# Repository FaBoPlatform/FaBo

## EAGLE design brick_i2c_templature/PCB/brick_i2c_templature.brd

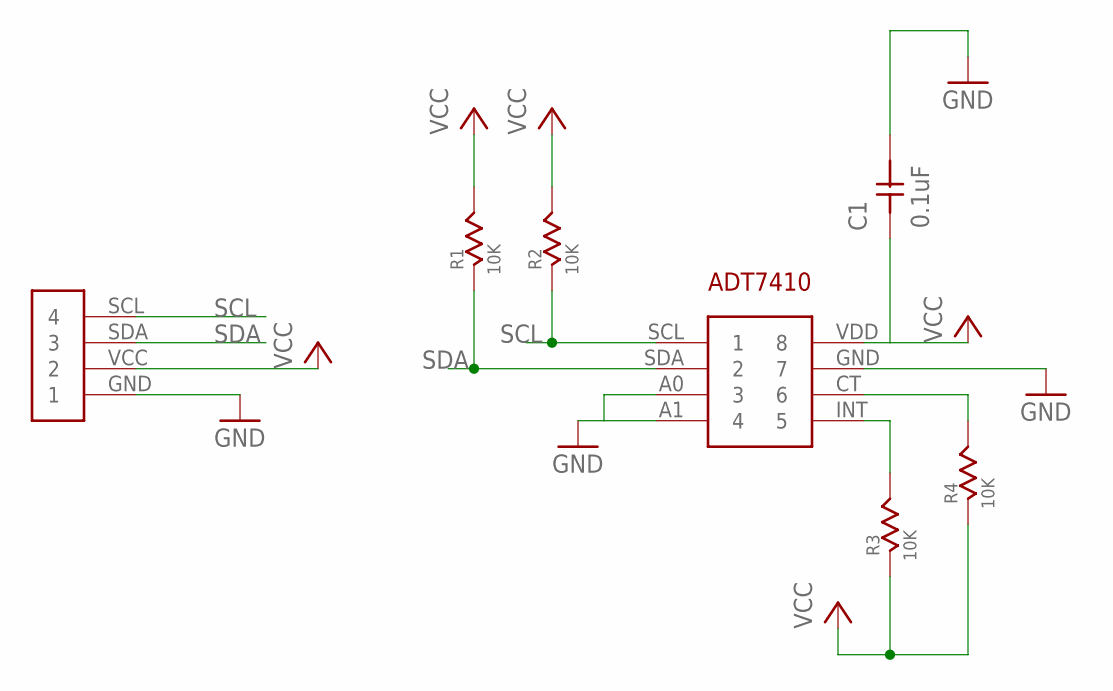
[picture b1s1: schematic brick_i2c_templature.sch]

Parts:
C1: 0.1uF; RESISTOR_0603
R1, R2, R3, R4: 10K; RESISTOR_0603
U$1: I2C-ADT7410
U$2: BRICK_I2C

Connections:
GND: C1.P$2, U$1.A0 (3), U$1.A1 (4), U$1.GND (7), U$2.GND (1)
unnamed: R3.P$2 (2), U$1.INT (5)
unnamed: R4.P$2 (2), U$1.CT (6)
SCL: R2.P$1 (1), U$1.SCL (1), U$2.SCL (4)
SDA: R1.P$1 (1), U$1.SDA (2), U$2.SDA (3)
VCC: C1.P$1, R1.P$2 (2), R2.P$2 (2), R3.P$1 (1), R4.P$1 (1), U$1.VDD (8), U$2.VCC (2)

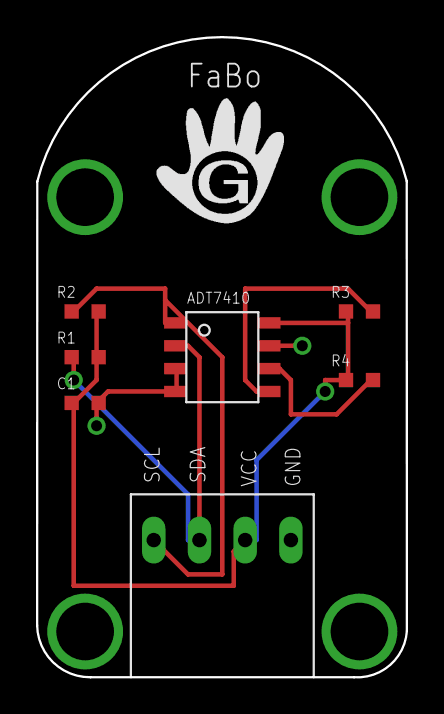
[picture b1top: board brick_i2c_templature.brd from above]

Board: 2 copper layers, 20.5 x 35.6 mm, 7 parts (0 on the bottom side), 6 nets.

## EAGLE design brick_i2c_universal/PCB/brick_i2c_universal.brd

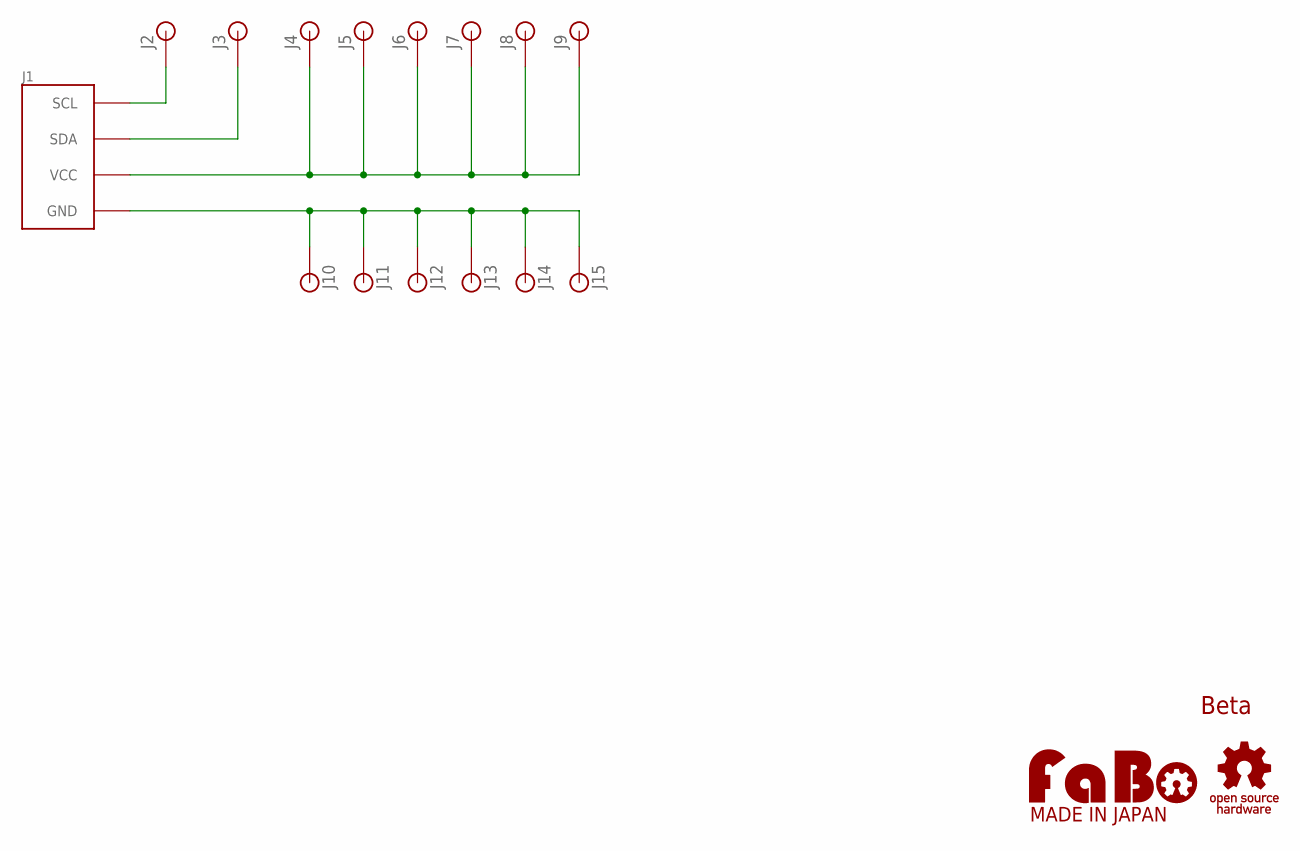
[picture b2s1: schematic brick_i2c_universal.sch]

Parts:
J1: FABO_BRICK_I2C-UNIVERSAL; FABO_BRICK_I2C_UNIVERSAL
J2, J3, J4, J5, J6, J7, J8, J9, J10, J11, J12, J13, J14, J15: PINHEAD_1X1-NONAME; PIN_1X1_NONAME
U$16: LOGO_OSHW-S_BOTTOM; LOGO_OSHW_S_BOTTOM
U$17: LOGO_FABO-M_BOTTOM; LOGO_FABO_M_BOTTOM

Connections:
GND: J1.GND, J10.1, J11.1, J12.1, J13.1, J14.1, J15.1
SCL: J1.SCL, J2.1
SDA: J1.SDA, J3.1
VCC: J1.VCC, J4.1, J5.1, J6.1, J7.1, J8.1, J9.1

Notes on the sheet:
Beta

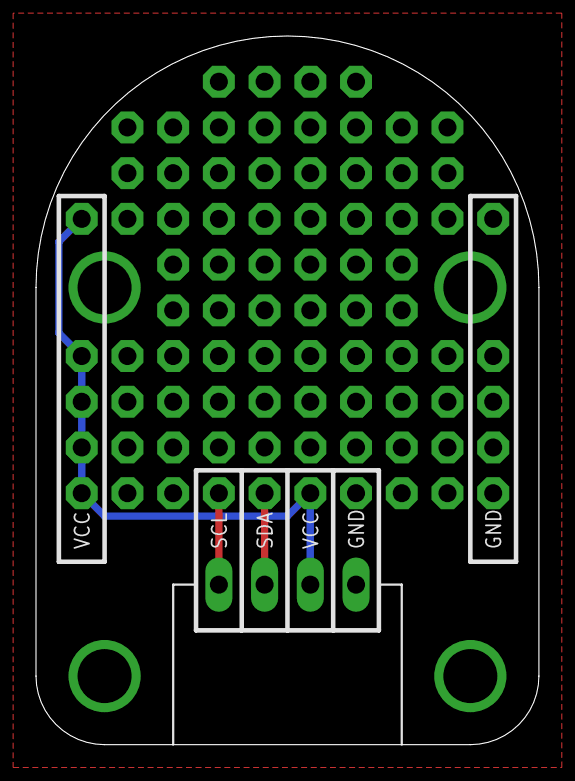
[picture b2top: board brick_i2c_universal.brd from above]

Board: 2 copper layers, 27.9 x 39.4 mm, 17 parts (0 on the bottom side), 4 nets.

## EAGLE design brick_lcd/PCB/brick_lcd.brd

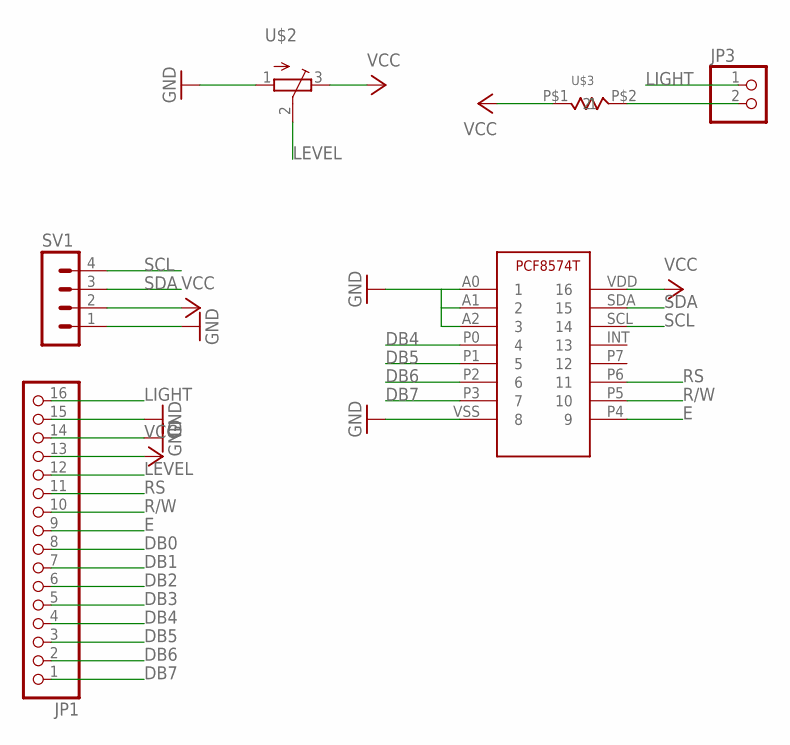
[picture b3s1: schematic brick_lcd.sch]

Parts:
JP1: PINHD-1X16; 1X16
JP3: PINHD-1X2; 1X02
SV1: MA04-1
U$1: IC-PCF8574T; SO16
U$2: TRIMPOTTC33X; TC33X
U$3: RESISTOR_0603

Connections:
DB0: JP1.8
DB1: JP1.7
DB2: JP1.6
DB3: JP1.5
DB4: JP1.4, U$1.P0 (4)
DB5: JP1.3, U$1.P1 (5)
DB6: JP1.2, U$1.P2 (6)
DB7: JP1.1, U$1.P3 (7)
E: JP1.9, U$1.P4 (9)
GND: JP1.14, JP1.15, SV1.1, U$1.A0 (1), U$1.A1 (2), U$1.A2 (3), U$1.VSS (8), U$2.1 (A)
LEVEL: JP1.12, U$2.2 (S)
LIGHT: JP1.16, JP3.1
unnamed: JP3.2, U$3.P$2 (2)
R/W: JP1.10, U$1.P5 (10)
RS: JP1.11, U$1.P6 (11)
SCL: SV1.4, U$1.SCL (14)
SDA: SV1.3, U$1.SDA (15)
VCC: JP1.13, SV1.2, U$1.VDD (16), U$2.3 (E), U$3.P$1 (1)

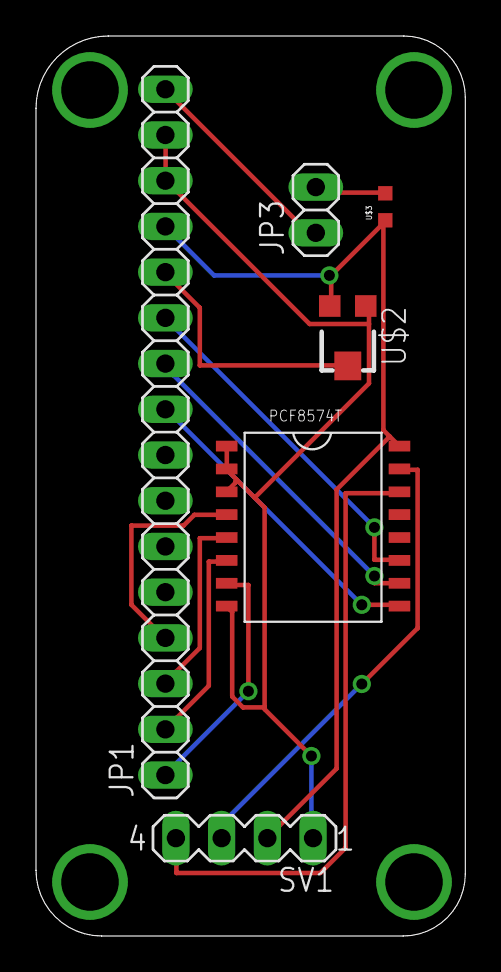
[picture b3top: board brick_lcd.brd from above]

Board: 2 copper layers, 23.9 x 50.0 mm, 6 parts (0 on the bottom side), 14 nets.

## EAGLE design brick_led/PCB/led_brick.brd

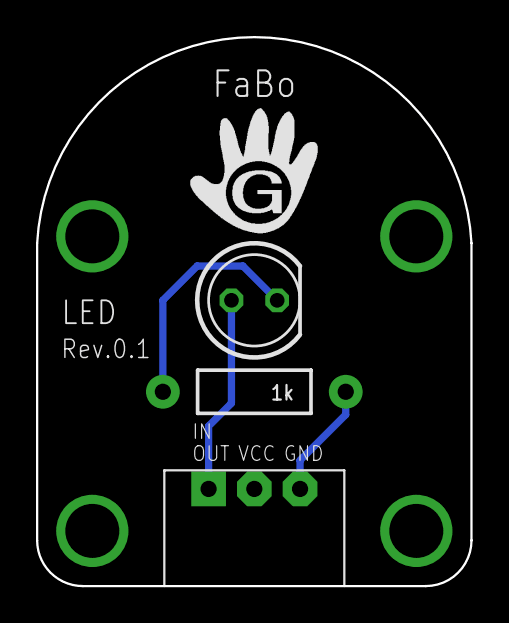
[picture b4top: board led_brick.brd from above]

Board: 2 copper layers, 24.1 x 30.5 mm, 3 parts (0 on the bottom side), 3 nets.

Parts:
J1: BRICK_3PIN
LED1: LED5MM
R1: 1k; AXIAL-0.4

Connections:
GND: J1.GND, R1.P$1
unnamed: J1.IN/OUT, LED1.A
unnamed: LED1.K, R1.P$2

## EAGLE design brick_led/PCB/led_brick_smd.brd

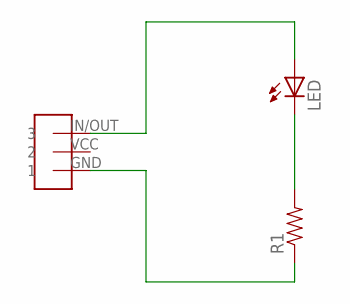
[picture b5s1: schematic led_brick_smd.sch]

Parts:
LED: LEDCHIP-LED0603; CHIP-LED0603
R1: RESISTOR0603-RES; 0603-RES
U$1: BRICK-3PIN; BRICK_3PIN

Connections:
GND: R1.1, U$1.GND (1)
unnamed: LED.A, U$1.IN/OUT (3)
unnamed: LED.C, R1.2

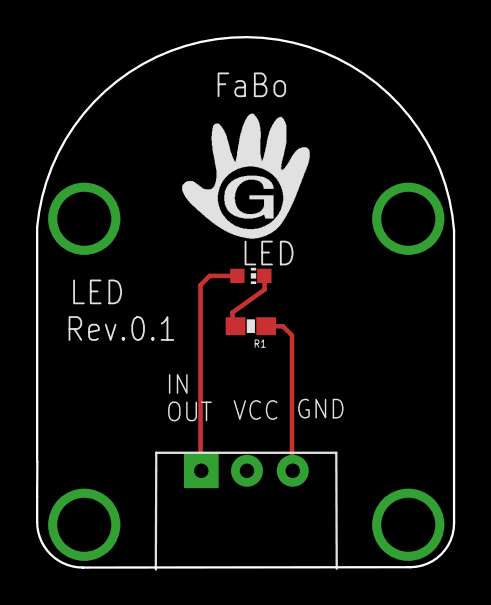
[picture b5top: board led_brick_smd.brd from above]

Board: 2 copper layers, 23.2 x 29.5 mm, 3 parts (0 on the bottom side), 3 nets.

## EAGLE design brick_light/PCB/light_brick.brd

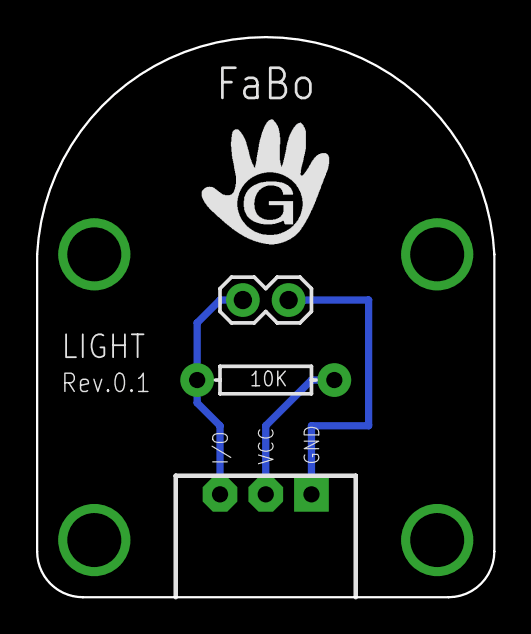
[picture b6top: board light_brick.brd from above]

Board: 2 copper layers, 25.4 x 31.1 mm, 3 parts (0 on the bottom side), 3 nets.

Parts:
J1: BRICK_3PIN
R1: 10K; AXIAL-0.3
U1: 1X02

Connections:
GND: J1.GND, U1.2
unnamed: J1.VCC, R1.P$1
unnamed: J1.IN/OUT, R1.P$2, U1.1

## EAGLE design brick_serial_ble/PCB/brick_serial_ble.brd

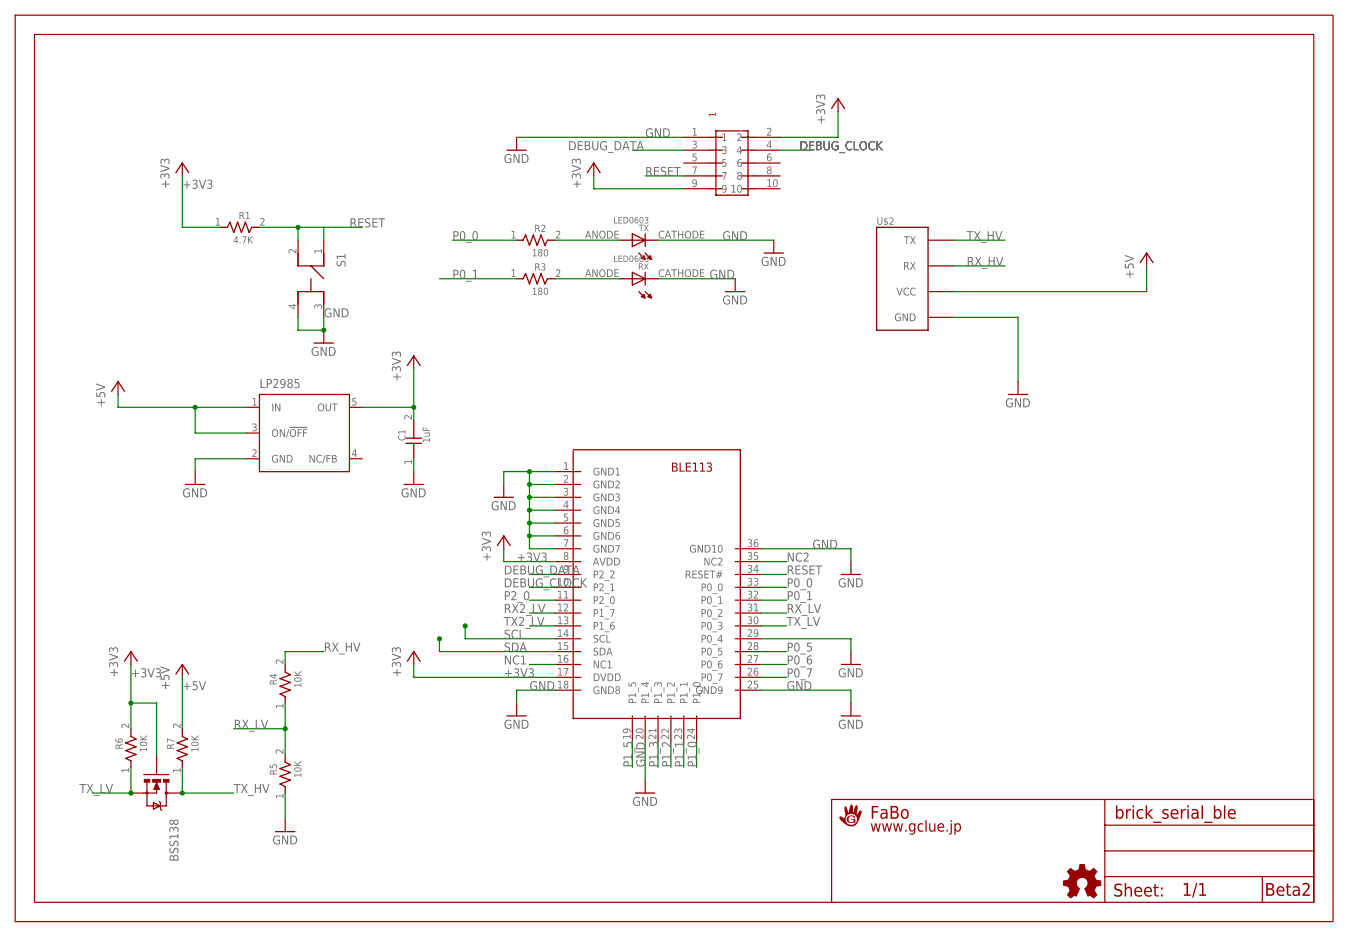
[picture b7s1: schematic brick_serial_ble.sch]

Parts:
BSS138: MOSFET-NCHANNELSMD; SOT23-3
C1: 1uF; 0603
LP2985: LP2985-XXDBVR33; SOT23-DBV
R1: 4.7K; 0603
R2, R3: 180; 0603
R4, R5, R6, R7: 10K; 0603
RX: LED0603; 0603
S1: SWITCH-LS6J2M-T
TX: LED0603; 0603
U$1: PIN-HEADER-SMT(1.27MM)2X5
U$2: BRICK_SERIAL
U$4: LOGO_OSHW-S; LOGO_OSHW_S
U$5: A4L-LOC-FABO_S; LOGO_FABO_S
U$6: BLUEGIGA-BLE113

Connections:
+3V3: BSS138.1 (G), C1.2, LP2985.5 (OUT), R1.1, R6.2, U$1.2, U$1.9, U$6.8 (AVDD), U$6.17 (DVDD)
+5V: LP2985.1 (IN), LP2985.3 (ON/!OFF), R7.2, U$2.VCC
DEBUG_CLOCK: U$1.4, U$6.10 (P2_1)
DEBUG_DATA: U$1.3, U$6.9 (P2_2)
GND: C1.1, LP2985.2 (GND), R5.1, RX.CATHODE, S1.3, S1.4, TX.CATHODE, U$1.1, U$2.GND, U$6.1 (GND1), U$6.2 (GND2), U$6.3 (GND3), U$6.4 (GND4), U$6.5 (GND5), U$6.6 (GND6), U$6.7 (GND7), U$6.18 (GND8), U$6.20 (P1_4), U$6.25 (GND9), U$6.29 (P0_4), U$6.36 (GND10)
unnamed: R2.2, TX.ANODE
unnamed: R3.2, RX.ANODE
NC1: U$6.16 (NC1)
NC2: U$6.35 (NC2)
P0_0: R2.1, U$6.33 (P0_0)
P0_1: R3.1, U$6.32 (P0_1)
P0_5: U$6.28 (P0_5)
P0_6: U$6.27 (P0_6)
P0_7: U$6.26 (P0_7)
P1_0: U$6.24 (P1_0)
P1_1: U$6.23 (P1_1)
P1_2: U$6.22 (P1_2)
P1_3: U$6.21 (P1_3)
P1_5: U$6.19 (P1_5)
P2_0: U$6.11 (P2_0)
RESET: R1.2, S1.1, S1.2, U$1.7, U$6.34 (RESET#)
RX2_LV: U$6.12 (P1_7)
RX_HV: R4.2, U$2.RX
RX_LV: R4.1, R5.2, U$6.31 (P0_2)
SCL: U$6.14 (SCL)
SDA: U$6.15 (SDA)
TX2_LV: U$6.13 (P1_6)
TX_HV: BSS138.3 (D), R7.1, U$2.TX
TX_LV: BSS138.2 (S), R6.1, U$6.30 (P0_3)

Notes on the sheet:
Beta2

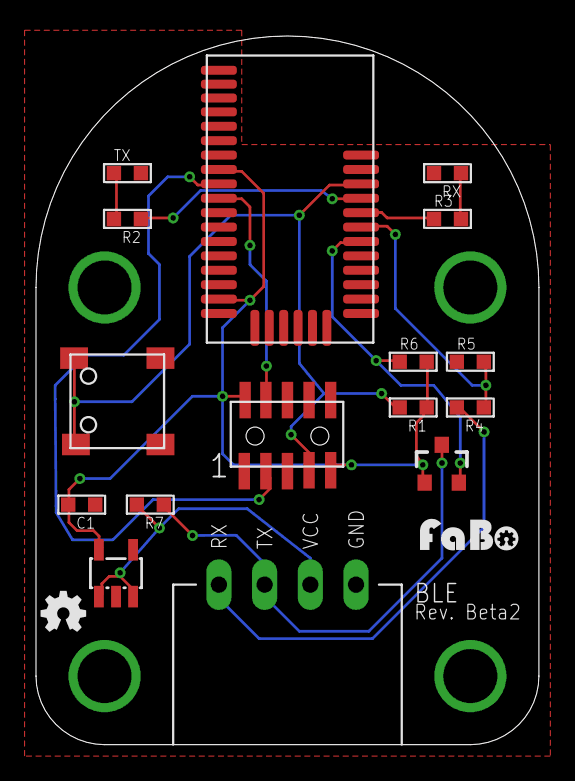
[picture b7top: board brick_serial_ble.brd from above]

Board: 2 copper layers, 27.9 x 39.4 mm, 18 parts (0 on the bottom side), 14 nets.

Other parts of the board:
U$3: LOGO_FABO_S

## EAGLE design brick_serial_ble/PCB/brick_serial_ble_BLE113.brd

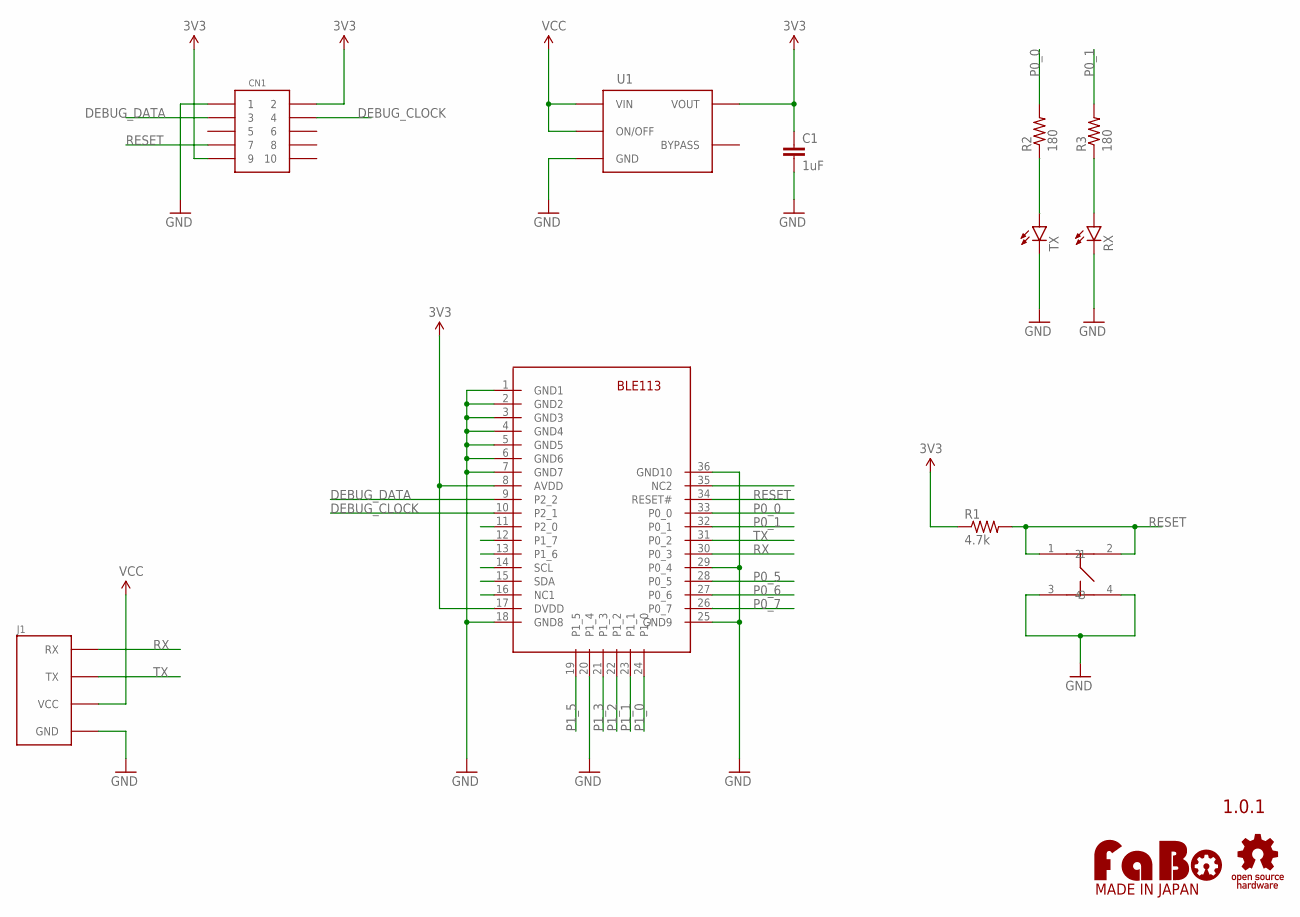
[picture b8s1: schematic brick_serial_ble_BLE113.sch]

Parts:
C1: 1uF; EIA0603
CN1: PIN-HEADER-SMT(1.27MM)2X5
J1: FABO_BRICK_SERIAL
R1: 4.7k; EIA0603
R2, R3: 180; EIA0603
RX: LED-EIA0603; EIA0603-LED
TX: LED-EIA0603; EIA0603-LED
U1: LP2985-33DBVR; SOT_23_5
U$2: LOGO_OSHW-T_M_BOTTOM; LOGO_OSHW_T_M_BOTTOM
U$3: LOGO_FABO-M_BOTTOM; LOGO_FABO_M_BOTTOM
U$6: BLUEGIGA-BLE113
U$7: SWICTH-4P(KMR2); SWITCH-4P(KMR2)

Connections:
3V3: C1.1, CN1.2, CN1.9, R1.1, U1.5 (VOUT), U$6.8 (AVDD), U$6.17 (DVDD)
DEBUG_CLOCK: CN1.4, U$6.10 (P2_1)
DEBUG_DATA: CN1.3, U$6.9 (P2_2)
GND: C1.2, CN1.1, J1.GND, RX.C, TX.C, U1.2 (GND), U$6.1 (GND1), U$6.2 (GND2), U$6.3 (GND3), U$6.4 (GND4), U$6.5 (GND5), U$6.6 (GND6), U$6.7 (GND7), U$6.18 (GND8), U$6.20 (P1_4), U$6.25 (GND9), U$6.29 (P0_4), U$6.36 (GND10), U$7.3, U$7.4
unnamed: R2.1, TX.A
unnamed: R3.1, RX.A
NC1: U$6.16 (NC1)
NC2: U$6.35 (NC2)
P0_0: R2.2, U$6.33 (P0_0)
P0_1: R3.2, U$6.32 (P0_1)
P0_5: U$6.28 (P0_5)
P0_6: U$6.27 (P0_6)
P0_7: U$6.26 (P0_7)
P1_0: U$6.24 (P1_0)
P1_1: U$6.23 (P1_1)
P1_2: U$6.22 (P1_2)
P1_3: U$6.21 (P1_3)
P1_5: U$6.19 (P1_5)
P2_0: U$6.11 (P2_0)
RESET: CN1.7, R1.2, U$6.34 (RESET#), U$7.1, U$7.2
RX: J1.RX, U$6.30 (P0_3)
RX2_LV: U$6.12 (P1_7)
SCL: U$6.14 (SCL)
SDA: U$6.15 (SDA)
TX: J1.TX, U$6.31 (P0_2)
TX2_LV: U$6.13 (P1_6)
VCC: J1.VCC, U1.1 (VIN), U1.3 (ON/OFF)

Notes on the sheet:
1.0.1

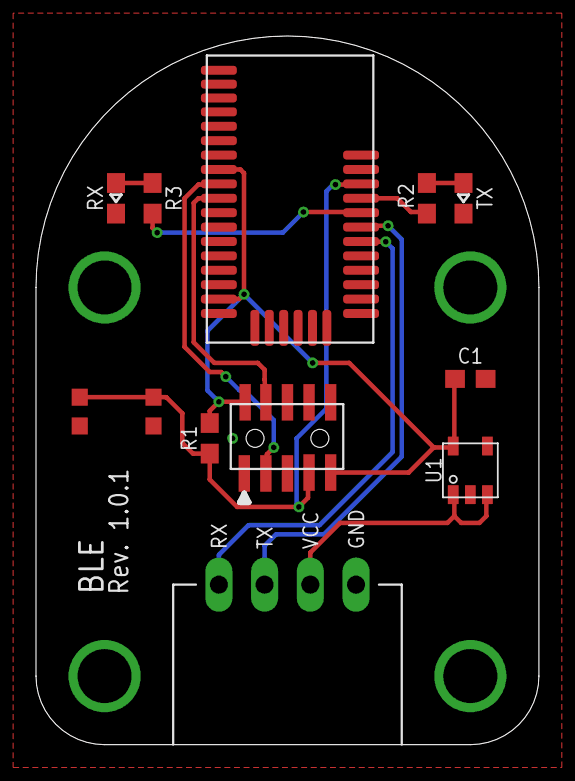
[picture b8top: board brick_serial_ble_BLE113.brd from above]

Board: 2 copper layers, 27.9 x 39.4 mm, 13 parts (0 on the bottom side), 12 nets.

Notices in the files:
parts and their libraries:
FaBo-etc: Released under the Creative Commons Attribution-ShareAlike 4.0 License
https://creativecommons.org/licenses/by-sa/4.0
FaBo-etc: Released under the Creative Commons
SparkFun-Resistors: Licensing: Creative Commons ShareAlike 4.0 International - https://creativecommons.org/licenses/by-sa/4.0
